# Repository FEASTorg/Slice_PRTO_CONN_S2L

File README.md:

# Prototyping Slice

Terminal connectors.

BREAD slice for creating new BREAD slices.

## Introduction

[Short introduction on the project.]

## Usage

[Explain how to use the project. Include examples and screenshots if applicable.]

## Documentation

Please refer to the [docs](/docs) for more info.

---

<div align="center">
  
</div>

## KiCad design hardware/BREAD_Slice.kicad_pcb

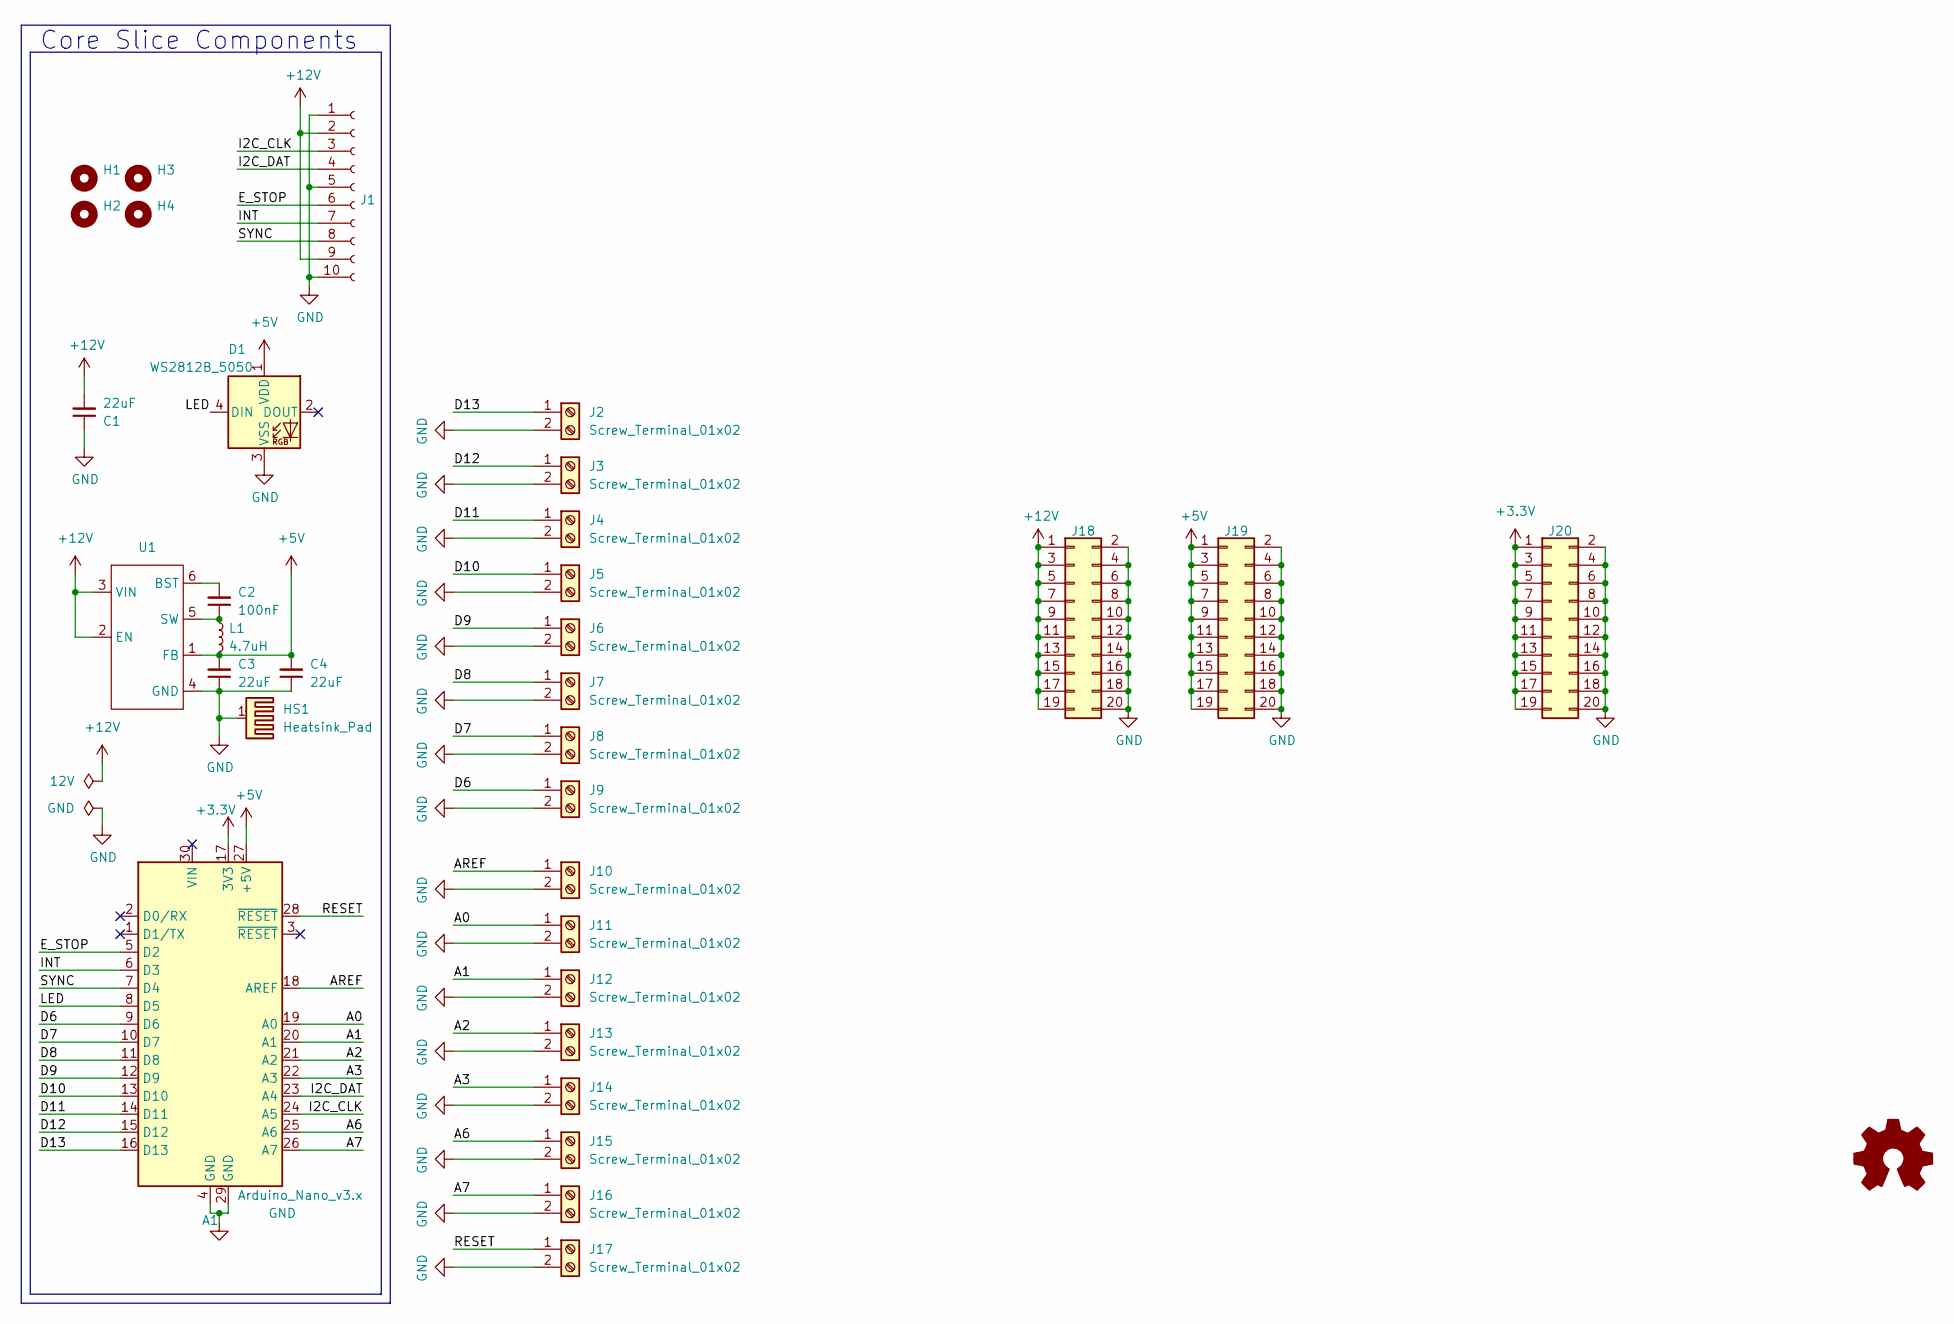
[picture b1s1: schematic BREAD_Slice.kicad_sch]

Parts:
A1: Arduino_Nano_v3.x; Arduino_Nano_Headers
C1, C3, C4: 22uF; C_1206_3216Metric
C2: 100nF; C_1206_3216Metric
D1: WS2812B_5050; WS2812-5050-4PIN
H1, H2, H3, H4: MountingHole; MountingHole_5mm
HS1: Heatsink_Pad; Thermal_Pad
J1: Conn_01x10_Female; PinSocket_1x10_P2.54mm_Horizontal
J2, J3, J4, J5, J6, J7, J8, J9, J10, J11, J12, J13, J14, J15, J16, J17: Screw_Terminal_01x02; TerminalBlock_TE_282834-2_1x02_P2.54mm_Horizontal
J18, J19, J20: Conn_02x10_Odd_Even; PinHeader_2x10_P2.54mm_Vertical
L1: 4.7uH; L_1210_3225Metric
U1: TSOT-23-6

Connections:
+3.3V: A1.17 (3V3), J20.1, J20.3, J20.5, J20.7, J20.9, J20.11, J20.13, J20.15, J20.17, J20.19
+5V: A1.27 (+5V), C3.2, C4.2, D1.1 (VDD), J19.1, J19.3, J19.5, J19.7, J19.9, J19.11, J19.13, J19.15, J19.17, J19.19, L1.2, U1.1 (FB)
+12V: C1.2, J1.2, J1.9, J18.1, J18.3, J18.5, J18.7, J18.9, J18.11, J18.13, J18.15, J18.17, J18.19, U1.2 (EN), U1.3 (VIN)
/A0: A1.19 (A0), J11.1
/A1: A1.20 (A1), J12.1
/A2: A1.21 (A2), J13.1
/A3: A1.22 (A3), J14.1
/A6: A1.25 (A6), J15.1
/A7: A1.26 (A7), J16.1
/AREF: A1.18 (AREF), J10.1
/D6: A1.9 (D6), J9.1
/D7: A1.10 (D7), J8.1
/D8: A1.11 (D8), J7.1
/D9: A1.12 (D9), J6.1
/D10: A1.13 (D10), J5.1
/D11: A1.14 (D11), J4.1
/D12: A1.15 (D12), J3.1
/D13: A1.16 (D13), J2.1
/E_STOP: A1.5 (D2), J1.6
/I2C_CLK: A1.24 (A5), J1.3
/I2C_DAT: A1.23 (A4), J1.4
/INT: A1.6 (D3), J1.7
/LED: A1.8 (D5), D1.4 (DIN)
/RESET: A1.28 (~RESET), J17.1
/SYNC: A1.7 (D4), J1.8
GND: A1.4 (GND), A1.29 (GND), C1.1, C3.1, C4.1, D1.3 (VSS), HS1.1, J1.1, J1.5, J1.10, J2.2, J3.2, J4.2, J5.2, J6.2, J7.2, J8.2, J9.2, J10.2, J11.2, J12.2, J13.2, J14.2, J15.2, J16.2, J17.2, J18.2, J18.4, J18.6, J18.8, J18.10, J18.12, J18.14, J18.16, J18.18, J18.20, J19.2, J19.4, J19.6, J19.8, J19.10, J19.12, J19.14, J19.16, J19.18, J19.20, J20.2, J20.4, J20.6, J20.8, J20.10, J20.12, J20.14, J20.16, J20.18, J20.20, U1.4 (GND)
unnamed: C2.2, U1.6 (BST)
unnamed: C2.1, L1.1, U1.5 (SW)

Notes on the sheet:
Core Slice Components

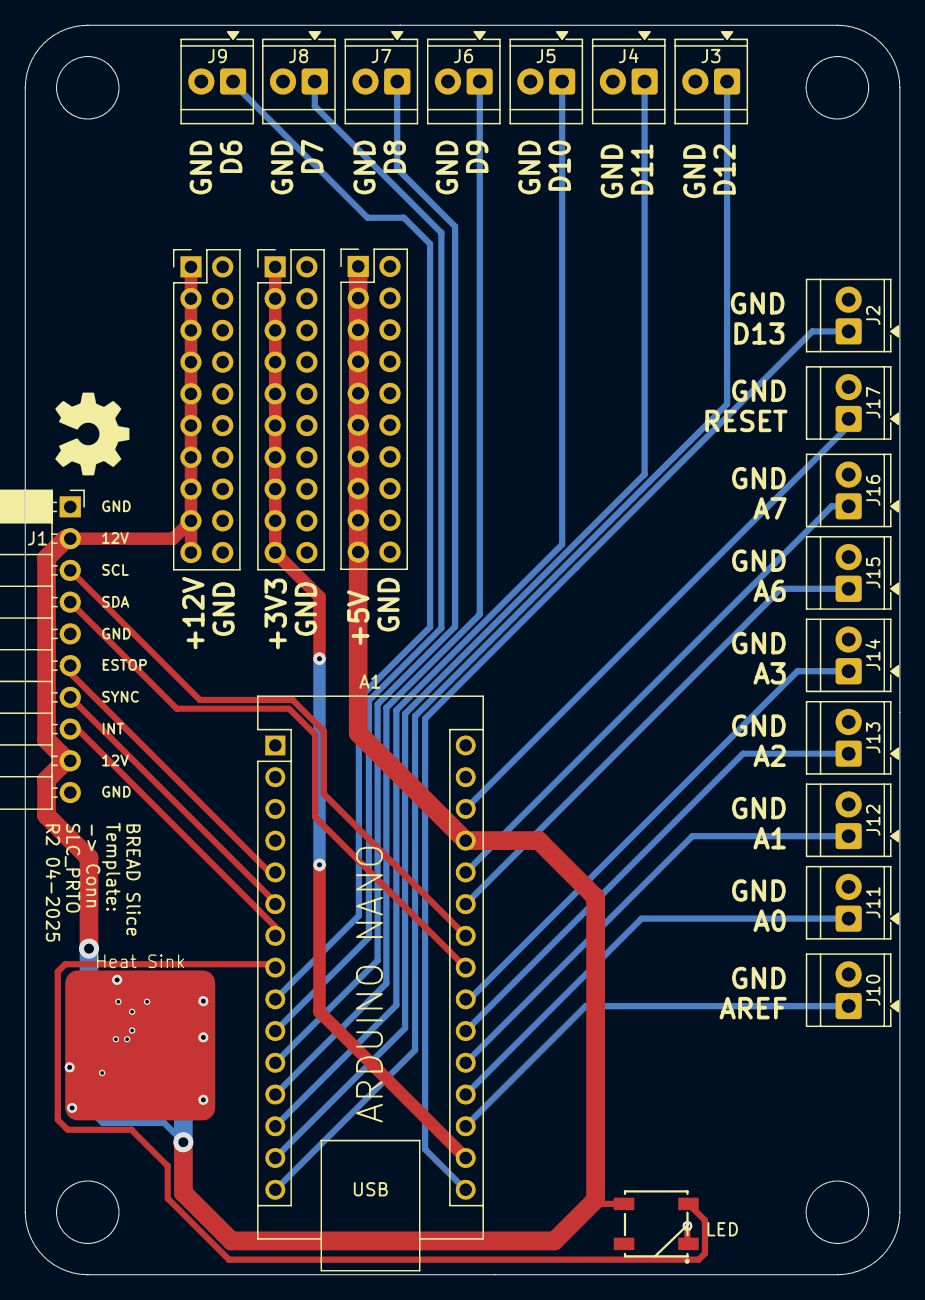
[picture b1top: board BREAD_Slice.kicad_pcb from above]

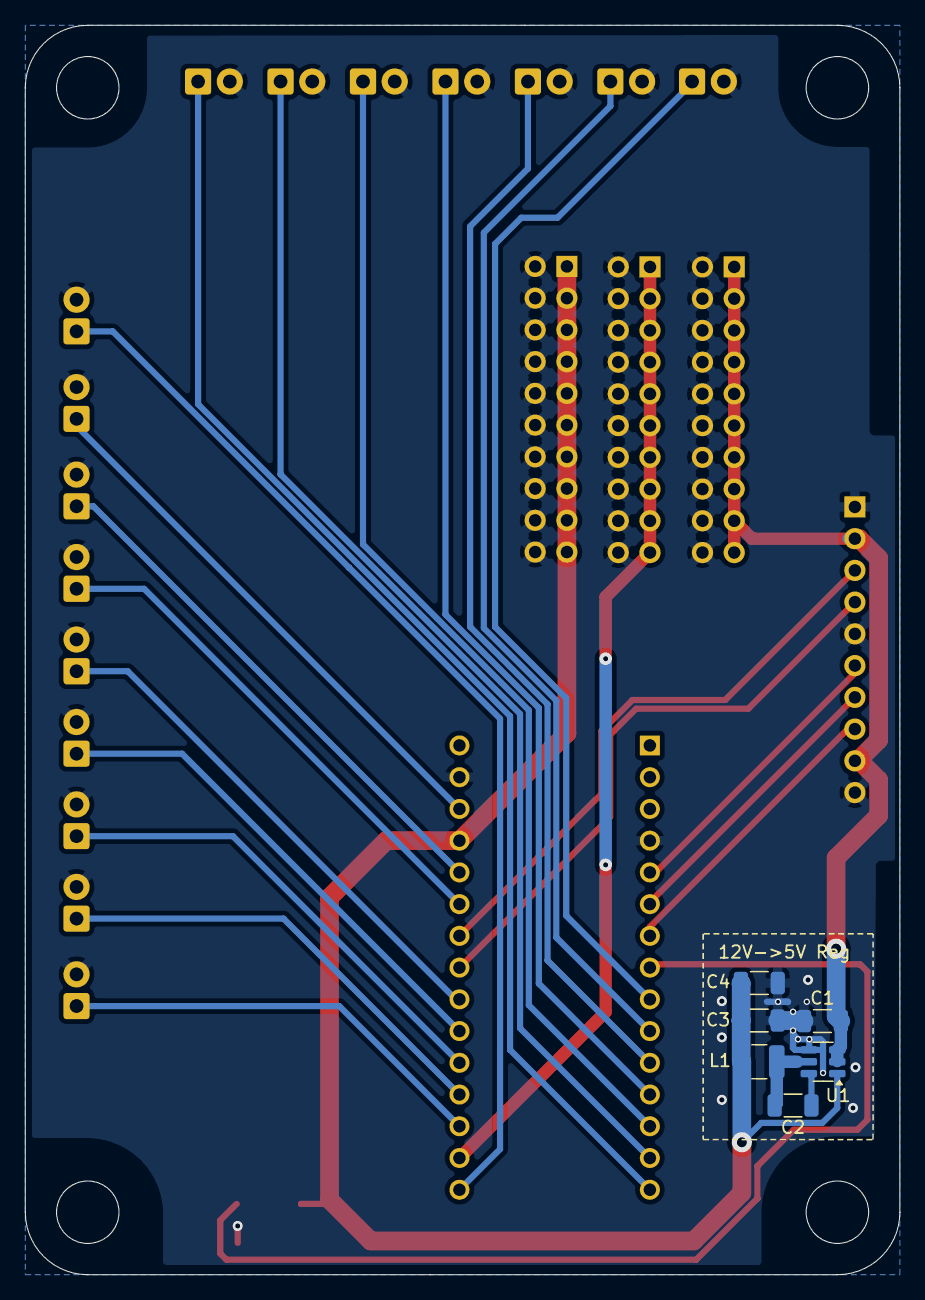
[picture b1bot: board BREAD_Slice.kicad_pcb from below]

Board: 2 copper layers, 70.0 x 100.0 mm, 34 parts (6 on the bottom side), 28 nets.

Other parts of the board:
Logo1: Logo_Open_Hardware_Small; OSHW-Symbol_6.7x6mm_SilkScreen

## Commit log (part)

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2025-09-24 initial commit after split
2025-09-24 ci: initial commit for gh pages bread-infra conv.
2025-09-24 📄 KiBot index + board renders (auto)
2025-09-24 update todo
2026-01-26 review and revise board and update footprints
2026-01-26 standard ignore
2026-04-20 refactor: org casing rename from 'FEASTorg' to 'feastorg'
2026-05-20 Add slice.yaml manifest (schema v1.0)
2026-05-24 Add standardized TODO.md with Pass 1/Pass 2 structure
